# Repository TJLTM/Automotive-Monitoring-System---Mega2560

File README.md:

# Automotive-Monitoring-System---Mega2560
OpenSource monitoring system for older vehicles without OBDII. History for this project to give some insight in why i have it designed it as i have. My dad has a 1972 ford bronco that is used to go 4x4ing and it has since the day he bought it new over heated on trails while his friends 1970 stock bronco would be idling behind his vapor locked car on the trail. Mostly this is to solve that problem by providing data. Given data systems can be fixed. I based this on a MEGA2560 because of the number of I/O pins and real time nature of this. I may in the future switch this to SBC based but so far other than a few limitations has worked. 

What is logged: 
1. Fuel Pressure x 2
2. Tempetatures x 6
3. Manifold Vacuum x 2
4. AFR x 2
5. Battery Voltage
6. Current drawn from Alternator 
7. RPM 
8. Oil Pressure
9. GPS Data

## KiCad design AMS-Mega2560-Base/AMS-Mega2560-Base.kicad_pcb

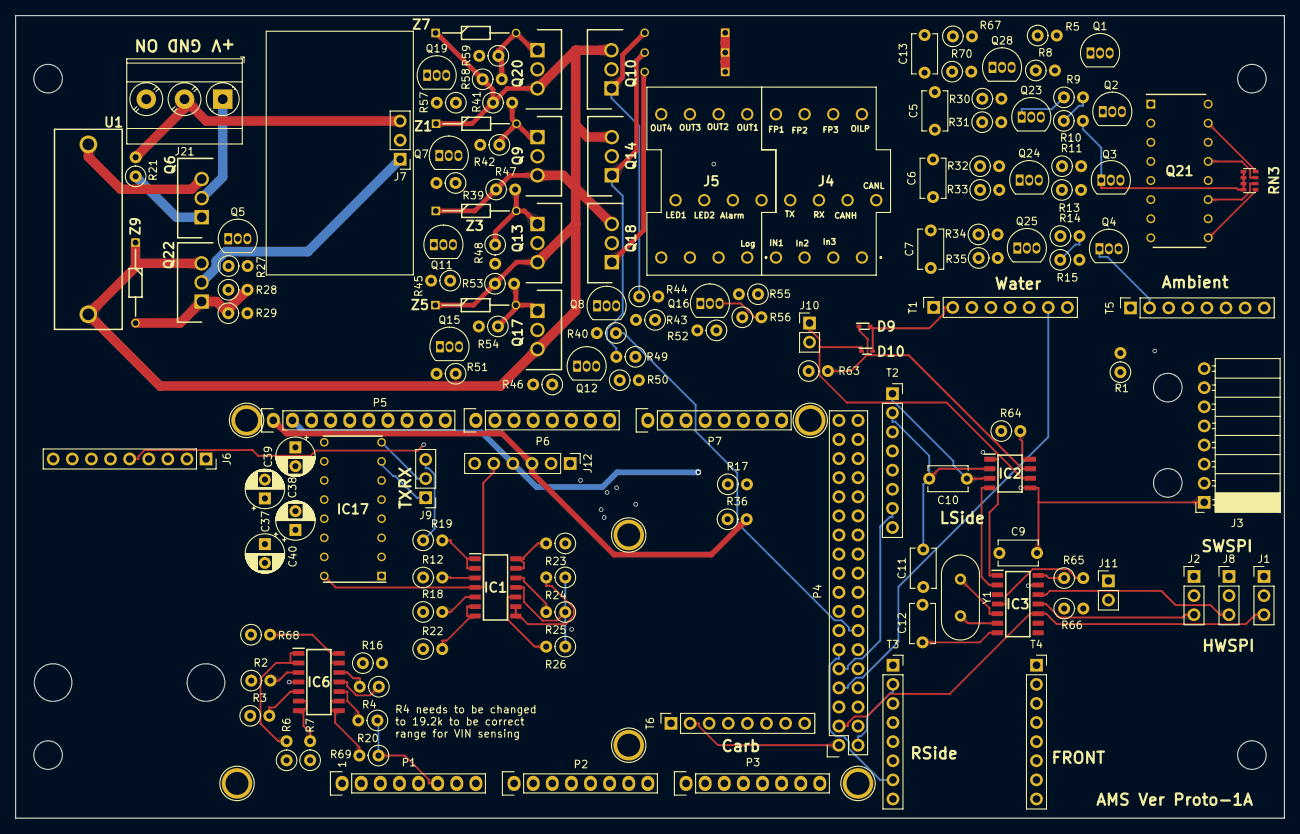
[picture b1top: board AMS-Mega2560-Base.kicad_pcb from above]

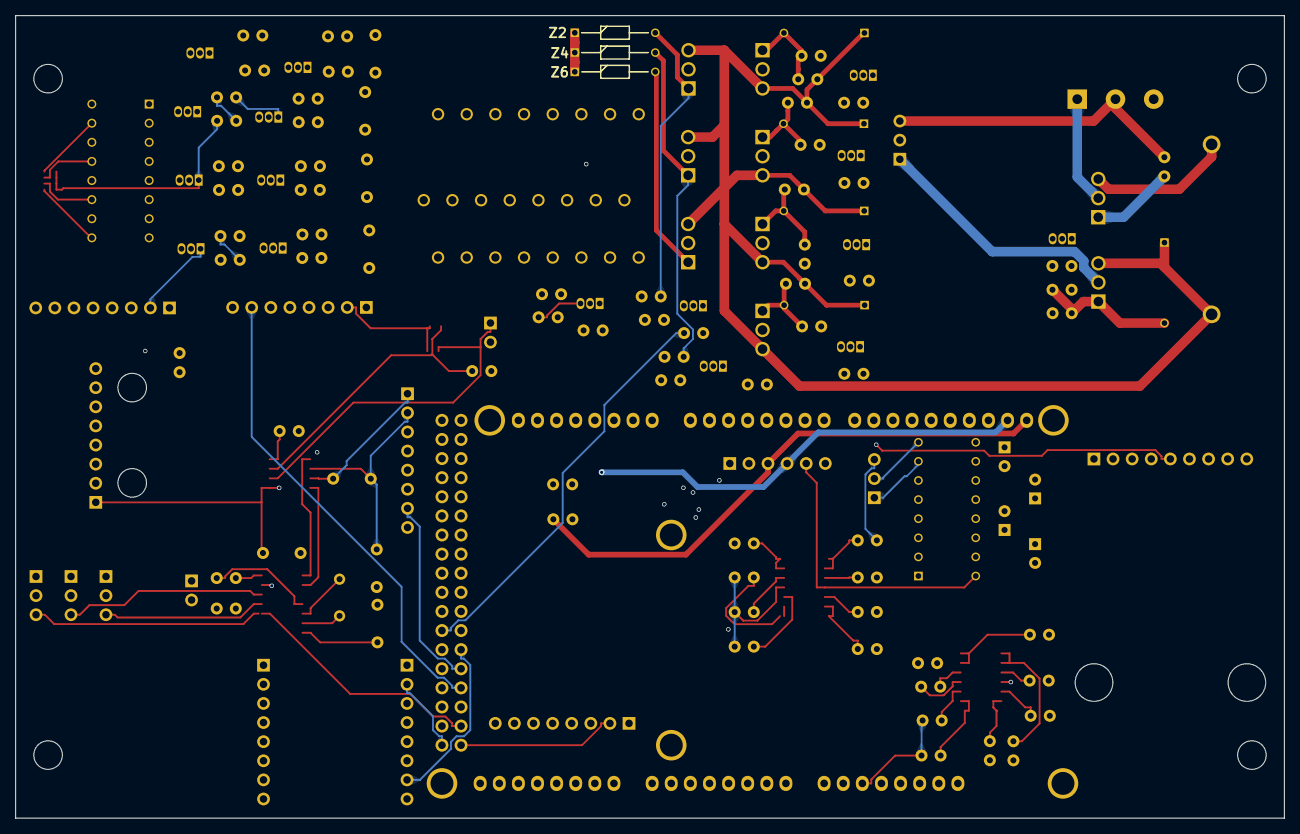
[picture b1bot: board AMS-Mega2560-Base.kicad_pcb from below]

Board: 4 copper layers, 168.7 x 106.7 mm, 153 parts (3 on the bottom side), 130 nets.

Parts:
C5, C6, C7, C13: 220nF; C_Disc_D5.1mm_W3.2mm_P5.00mm
C9: 0.1uF; C_Disc_D5.1mm_W3.2mm_P5.00mm
C10: 100nF; C_Disc_D5.1mm_W3.2mm_P5.00mm
C11, C12: 22pF; C_Disc_D5.1mm_W3.2mm_P5.00mm
C37, C38, C39, C40: 1uF; CP_Radial_D5.0mm_P2.50mm
D9, D10: ESD5Z5.0T1G; SODFL1608X70N
IC1, IC6: OPA4340UA; SOIC127P600X175-14N
IC2: MCP2542FD-H_SN; SOIC127P600X175-8N
IC3: MCP2518FDT-E_SL; SOIC127P600X175-14N
IC17: MAX232CPE+; DIP762W56P254L1918H457Q16N
J1, J2, J7, J8, J9: Conn_01x03; PinHeader_1x03_P2.54mm_Vertical
J3: Conn_01x08; PinSocket_1x08_P2.54mm_Horizontal
J4: Sense1; 1727751
J5: Sense2; 1727751
J6: AdafruitUltimateGPS; PinSocket_1x09_P2.54mm_Vertical
J10, J11: Conn_01x02; PinHeader_1x02_P2.54mm_Vertical
J12: Conn_01x06; PinHeader_1x06_P2.54mm_Vertical
J21: Screw_Terminal_01x03; TerminalBlock_Phoenix_MKDS-3-3-5.08_1x03_P5.08mm_Horizontal
P1: Power; Socket_Strip_Arduino_1x08
P2, P3: Analog; Socket_Strip_Arduino_1x08
P4: Digital; Socket_Strip_Arduino_2x18
P5: PWM; Socket_Strip_Arduino_1x10
P6: PWM; Socket_Strip_Arduino_1x08
P7: Communication; Socket_Strip_Arduino_1x08
P8, P9, P10, P11, P12, P13: CONN_01X01; Arduino_1pin
Q1, Q2, Q3, Q4, Q5, Q7, Q8, Q11, Q12, Q15, Q16, Q19: 2N7000; TO-92_Inline
Q6, Q9, Q10, Q13, Q14, Q17, Q18, Q20, Q22: IRF9Z34NPBF; TO254P469X1042X1967-3P
Q21: LTV-847; DIP762W60P254L1984H450Q16N
Q23, Q24, Q25, Q28: BS250; TO-92_Inline
R1, R6, R7, R19, R22, R23, R24, R68, R69: 47K; R_Axial_DIN0207_L6.3mm_D2.5mm_P2.54mm_Vertical
R2, R3, R4, R12, R18, R20, R25, R26: 100K; R_Axial_DIN0207_L6.3mm_D2.5mm_P2.54mm_Vertical
R5, R9, R11, R14: 470; R_Axial_DIN0207_L6.3mm_D2.5mm_P2.54mm_Vertical
R8, R10, R13, R15: 5k; R_Axial_DIN0207_L6.3mm_D2.5mm_P2.54mm_Vertical
R16, R65, R66: 47k; R_Axial_DIN0207_L6.3mm_D2.5mm_P2.54mm_Vertical
R17, R36: 2.2k; R_Axial_DIN0207_L6.3mm_D2.5mm_P2.54mm_Vertical
R21: 4.7K; R_Axial_DIN0207_L6.3mm_D2.5mm_P2.54mm_Vertical
R27, R28, R41, R43, R47, R49, R53, R55, R58: 100k; R_Axial_DIN0207_L6.3mm_D2.5mm_P2.54mm_Vertical
R29, R42, R44, R48, R50, R54, R56, R59, R64: 10k; R_Axial_DIN0207_L6.3mm_D2.5mm_P2.54mm_Vertical
R30, R32, R34, R67: 330; R_Axial_DIN0207_L6.3mm_D2.5mm_P2.54mm_Vertical
R31, R33, R35, R70: 1K; R_Axial_DIN0207_L6.3mm_D2.5mm_P2.54mm_Vertical
R39, R40, R45, R46, R51, R52, R57: 1M; R_Axial_DIN0207_L6.3mm_D2.5mm_P2.54mm_Vertical
R63: 120; R_Axial_DIN0207_L6.3mm_D2.5mm_P2.54mm_Vertical
RN3: EXB-38V223JV; EXB38V472JV
T1, T2, T3, T4, T5, T6: Conn_01x08; PinSocket_1x08_P2.54mm_Vertical
U1: BK_HTC-15M
Y1: Crystal; Crystal_HC49-U_Vertical
Z1, Z2, Z3, Z4, Z5, Z6, Z7, Z9: BZX79C10; DIOAD1068W53L380D172

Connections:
+5V: C9.2, C10.1, C40.2, IC1.4 (V+), IC2.3 (VDD), IC2.5 (VIO), IC3.14 (VDD), IC6.4 (V+), IC17.16 (VCC), J3.1, J6.8, J7.2, J12.5, P1.5, Q21.1 (ANODE_1), Q21.3 (ANODE_2), Q21.5 (ANODE_3), Q21.7 (ANODE_4), Q21.10 (COLLECTOR_1), Q21.12 (COLLECTOR_2), Q21.14 (COLLECTOR_3), Q21.16 (COLLECTOR_4), R1.1, R17.1, R36.1, R65.1, T1.1, T2.1, T3.1, T4.1, T5.1, T6.1
+VDC: Q9.3, Q10.3, Q13.3, Q14.3, Q17.3, Q18.3, Q20.3, Q22.3, R28.1, R41.1, R43.1, R47.1, R49.1, R53.1, R55.1, R58.1, U1.2, Z1.1, Z2.1, Z3.1, Z4.1, Z5.1, Z6.1, Z7.1, Z9.1
/BufferedADC1/ADCIN4: IC6.12 (+IN_D), R4.2, R16.2
/CAN Bus/CAN_INT: IC3.4 (~INT), J11.1, R65.2, R66.1
/Sheet6152913C/RSCOM2RX: IC17.8 (R2IN), J9.2
/Sheet6152913C/RSCOM2TX: IC17.7 (T2OUT), J9.1
AmbientCS: P4.15, T5.7
CANCS: IC3.13 (NCS), P4.23
CAN_INT: J11.2, P4.27
CAN_TX_STBY: IC2.8 (STBY), P4.25, R64.2
CarbCS: P4.17, T6.7
Com1RX: IC17.12 (R1OUT), P7.4
Com1TX: IC17.11 (T1IN), P7.3
Com2RX: IC17.9 (R2OUT), P7.6
Com2TX: IC17.10 (T2IN), P7.5
FrontCS: P4.13, T4.7
FuelPressure1: IC6.1 (OUT_A), IC6.2 (-IN_A), P2.3, R6.2
FuelPressure2: IC6.6 (-IN_B), IC6.7 (OUT_B), P2.4, R7.2
FuelPressure3: IC6.8 (OUT_C), IC6.9 (-IN_C), P2.5, R69.2
GND: C5.2, C6.2, C7.2, C9.1, C10.2, C11.2, C12.2, C13.2, C39.1, D9.2, D10.2, IC1.11 (V-), IC2.2 (VSS), IC3.7 (VSS), IC6.11 (V-), IC17.15 (GND), J3.3, J6.7, J7.3, J9.3, J12.6, J21.2, P1.6, P1.7, P4.1, P4.2, P5.4, Q1.1 (S), Q2.1 (S), Q3.1 (S), Q4.1 (S), Q5.1 (S), Q7.1 (S), Q8.1 (S), Q11.1 (S), Q12.1 (S), Q15.1 (S), Q16.1 (S), Q19.1 (S), R2.1, R3.1, R4.1, R6.1, R7.1, R8.2, R10.2, R12.1, R13.2, R15.2, R18.1, R19.1, R20.1, R21.2, R22.1, R23.1, R24.1, R25.1, R26.1, R27.2, R30.2, R32.2, R34.2, R39.2, R40.2, R45.2, R46.2, R51.2, R52.2, R57.2, R64.1, R66.2, R67.2, R68.1, R69.1, RN3.1, RN3.2, RN3.3, RN3.4, T1.2, T2.2, T3.2, T4.2, T5.2, T6.2
GPSBat: J6.3, P2.2
GPSRX: J6.6, P7.1
GPSTX: J6.5, P7.2
IN1TTL: P6.6, Q21.15 (EMITTER_4), RN3.8
IN2TTL: P6.5, Q21.13 (EMITTER_3), RN3.7
IN3TTL: P4.10, Q21.11 (EMITTER_2), RN3.6
Logging: P4.8, Q21.9 (EMITTER_1), RN3.5
LsideCS: P4.9, T2.7
MISO: IC3.11 (SDI), J2.3, J3.5, P4.5
MOSI: IC3.12 (SDO), J3.6, J8.3, P4.6
unnamed: J21.1, Q6.2
unnamed: Q6.3, U1.1
unnamed: C39.2, IC17.6 (V-)
unnamed: C40.1, IC17.2 (V+)
unnamed: IC2.4 (RXD), IC3.2 (RXCAN)
unnamed: IC2.1 (TXD), IC3.1 (TXCAN)
unnamed: C12.1, IC3.6 (OSC1), Y1.2
unnamed: C11.1, IC3.5 (OSC2), Y1.1
unnamed: C37.1, IC17.1 (C1+)
unnamed: C37.2, IC17.3 (C1-)
unnamed: C38.1, IC17.4 (C2+)
unnamed: C38.2, IC17.5 (C2-)
unnamed: J10.2, R63.1
unnamed: Q1.3 (D), R70.1
unnamed: Q1.2 (G), R5.2, R8.1
unnamed: Q2.3 (D), R31.1
unnamed: Q2.2 (G), R9.2, R10.1
unnamed: Q3.3 (D), R33.1
unnamed: Q3.2 (G), R11.2, R13.1
unnamed: Q4.3 (D), R35.1
unnamed: Q4.2 (G), R14.2, R15.1
unnamed: Q5.3 (D), R29.2
unnamed: Q6.1, R21.1
unnamed: Q7.3 (D), R42.2
unnamed: Q8.3 (D), R44.2
unnamed: Q9.1, R41.2, R42.1, Z1.2
unnamed: Q10.1, R43.2, R44.1, Z2.2
unnamed: Q11.3 (D), R48.2
unnamed: Q12.3 (D), R50.2
unnamed: Q13.1, R47.2, R48.1, Z3.2
unnamed: Q14.1, R49.2, R50.1, Z4.2
unnamed: Q15.3 (D), R54.2
unnamed: Q16.3 (D), R56.2
unnamed: Q17.1, R53.2, R54.1, Z5.2
unnamed: Q18.1, R55.2, R56.1, Z6.2
unnamed: Q19.3 (D), R59.2
unnamed: Q20.1, R58.2, R59.1, Z7.2
unnamed: Q21.2 (CATHODE_1), R70.2
unnamed: Q21.4 (CATHODE_2), R31.2
unnamed: Q21.6 (CATHODE_3), R33.2
unnamed: Q21.8 (CATHODE_4), R35.2
unnamed: Q22.1, R28.2, R29.1, Z9.2
unnamed: Q23.1 (D), R9.1
unnamed: Q23.2 (G), R30.1
unnamed: Q24.1 (D), R11.1
unnamed: Q24.2 (G), R32.1
unnamed: Q25.1 (D), R14.1
unnamed: Q25.2 (G), R34.1
unnamed: Q28.1 (D), R5.1
unnamed: Q28.2 (G), R67.1
OUTPUT1: P6.4, Q19.2 (G), R57.1
OUTPUT2: P6.3, Q7.2 (G), R39.1
OUTPUT3: P6.2, Q11.2 (G), R45.1
OUTPUT4: P6.1, Q15.2 (G), R51.1
OUTPUTLED1: P4.14, Q8.2 (G), R40.1
OUTPUTLED2: P4.12, Q12.2 (G), R46.1
OUTPUTSiren: P5.10, Q16.2 (G), R52.1
OilPressure: IC1.1 (OUT_A), IC1.2 (-IN_A), P2.6, R19.2
PowerOn: J21.3, Q5.2 (G), R27.1
RTDMISO: J2.2, T1.5, T2.5, T3.5, T4.5, T5.5, T6.5
RTDMOSI: J8.2, T1.6, T2.6, T3.6, T4.6, T5.6, T6.6
RTDSCLK: J1.2, T1.4, T2.4, T3.4, T4.4, T5.4, T6.4
RsideCS: P4.11, T3.7
SCL: J12.3, P5.1, P7.8, R36.2
SCLK: IC3.10 (SCK), J1.3, J3.4, P4.3
SDA: J12.4, P5.2, P7.7, R17.2
SDCS: J3.7, P4.19
SDDetect: J3.8, P4.21, R1.2
SWMISO: J2.1, P4.32
SWMOSI: J8.1, P4.34
SWSCLK: J1.1, P4.30
Sense1-1: J4.1, P3.2
Sense1-2: D10.1, IC2.6 (CANL), J4.2, J10.1
Sense1-3: IC1.3 (+IN_A), J4.3, R12.2
Sense1-4: C6.1, J4.4, Q24.3 (S)
Sense1-5: D9.1, IC2.7 (CANH), J4.5, R63.2
Sense1-6: IC6.10 (+IN_C), J4.6, R20.2
Sense1-7: C5.1, J4.7, Q23.3 (S)
Sense1-8: IC17.13 (R1IN), J4.8
Sense1-9: IC6.5 (+IN_B), J4.9, R3.2
Sense1-10: C13.1, J4.10, Q28.3 (S)
Sense1-11: IC17.14 (T1OUT), J4.11
Sense1-12: IC6.3 (+IN_A), J4.12, R2.2
Sense2-1: C7.1, J5.1, Q25.3 (S)
Sense2-3: J5.3, Q20.2
Sense2-4: IC1.12 (+IN_D), J5.4, R25.2
Sense2-5: J5.5, Q18.2
Sense2-6: J5.6, Q9.2
Sense2-7: IC1.10 (+IN_C), J5.7, R26.2
Sense2-8: J5.8, Q14.2
Sense2-9: J5.9, Q13.2
Sense2-10: IC1.5 (+IN_B), J5.10, R18.2
Sense2-11: J5.11, Q10.2
Sense2-12: J5.12, Q17.2
SpareADC1: IC1.6 (-IN_B), IC1.7 (OUT_B), P2.7, R22.2
SpareADC2: IC1.8 (OUT_C), IC1.9 (-IN_C), P2.8, R24.2
SpareADC3: IC1.13 (-IN_D), IC1.14 (OUT_D), P3.1, R23.2
VPP: J7.1, Q22.2, R16.1
VoltageSensor: IC6.13 (-IN_D), IC6.14 (OUT_D), P2.1, R68.2
WaterCS: P4.7, T1.7

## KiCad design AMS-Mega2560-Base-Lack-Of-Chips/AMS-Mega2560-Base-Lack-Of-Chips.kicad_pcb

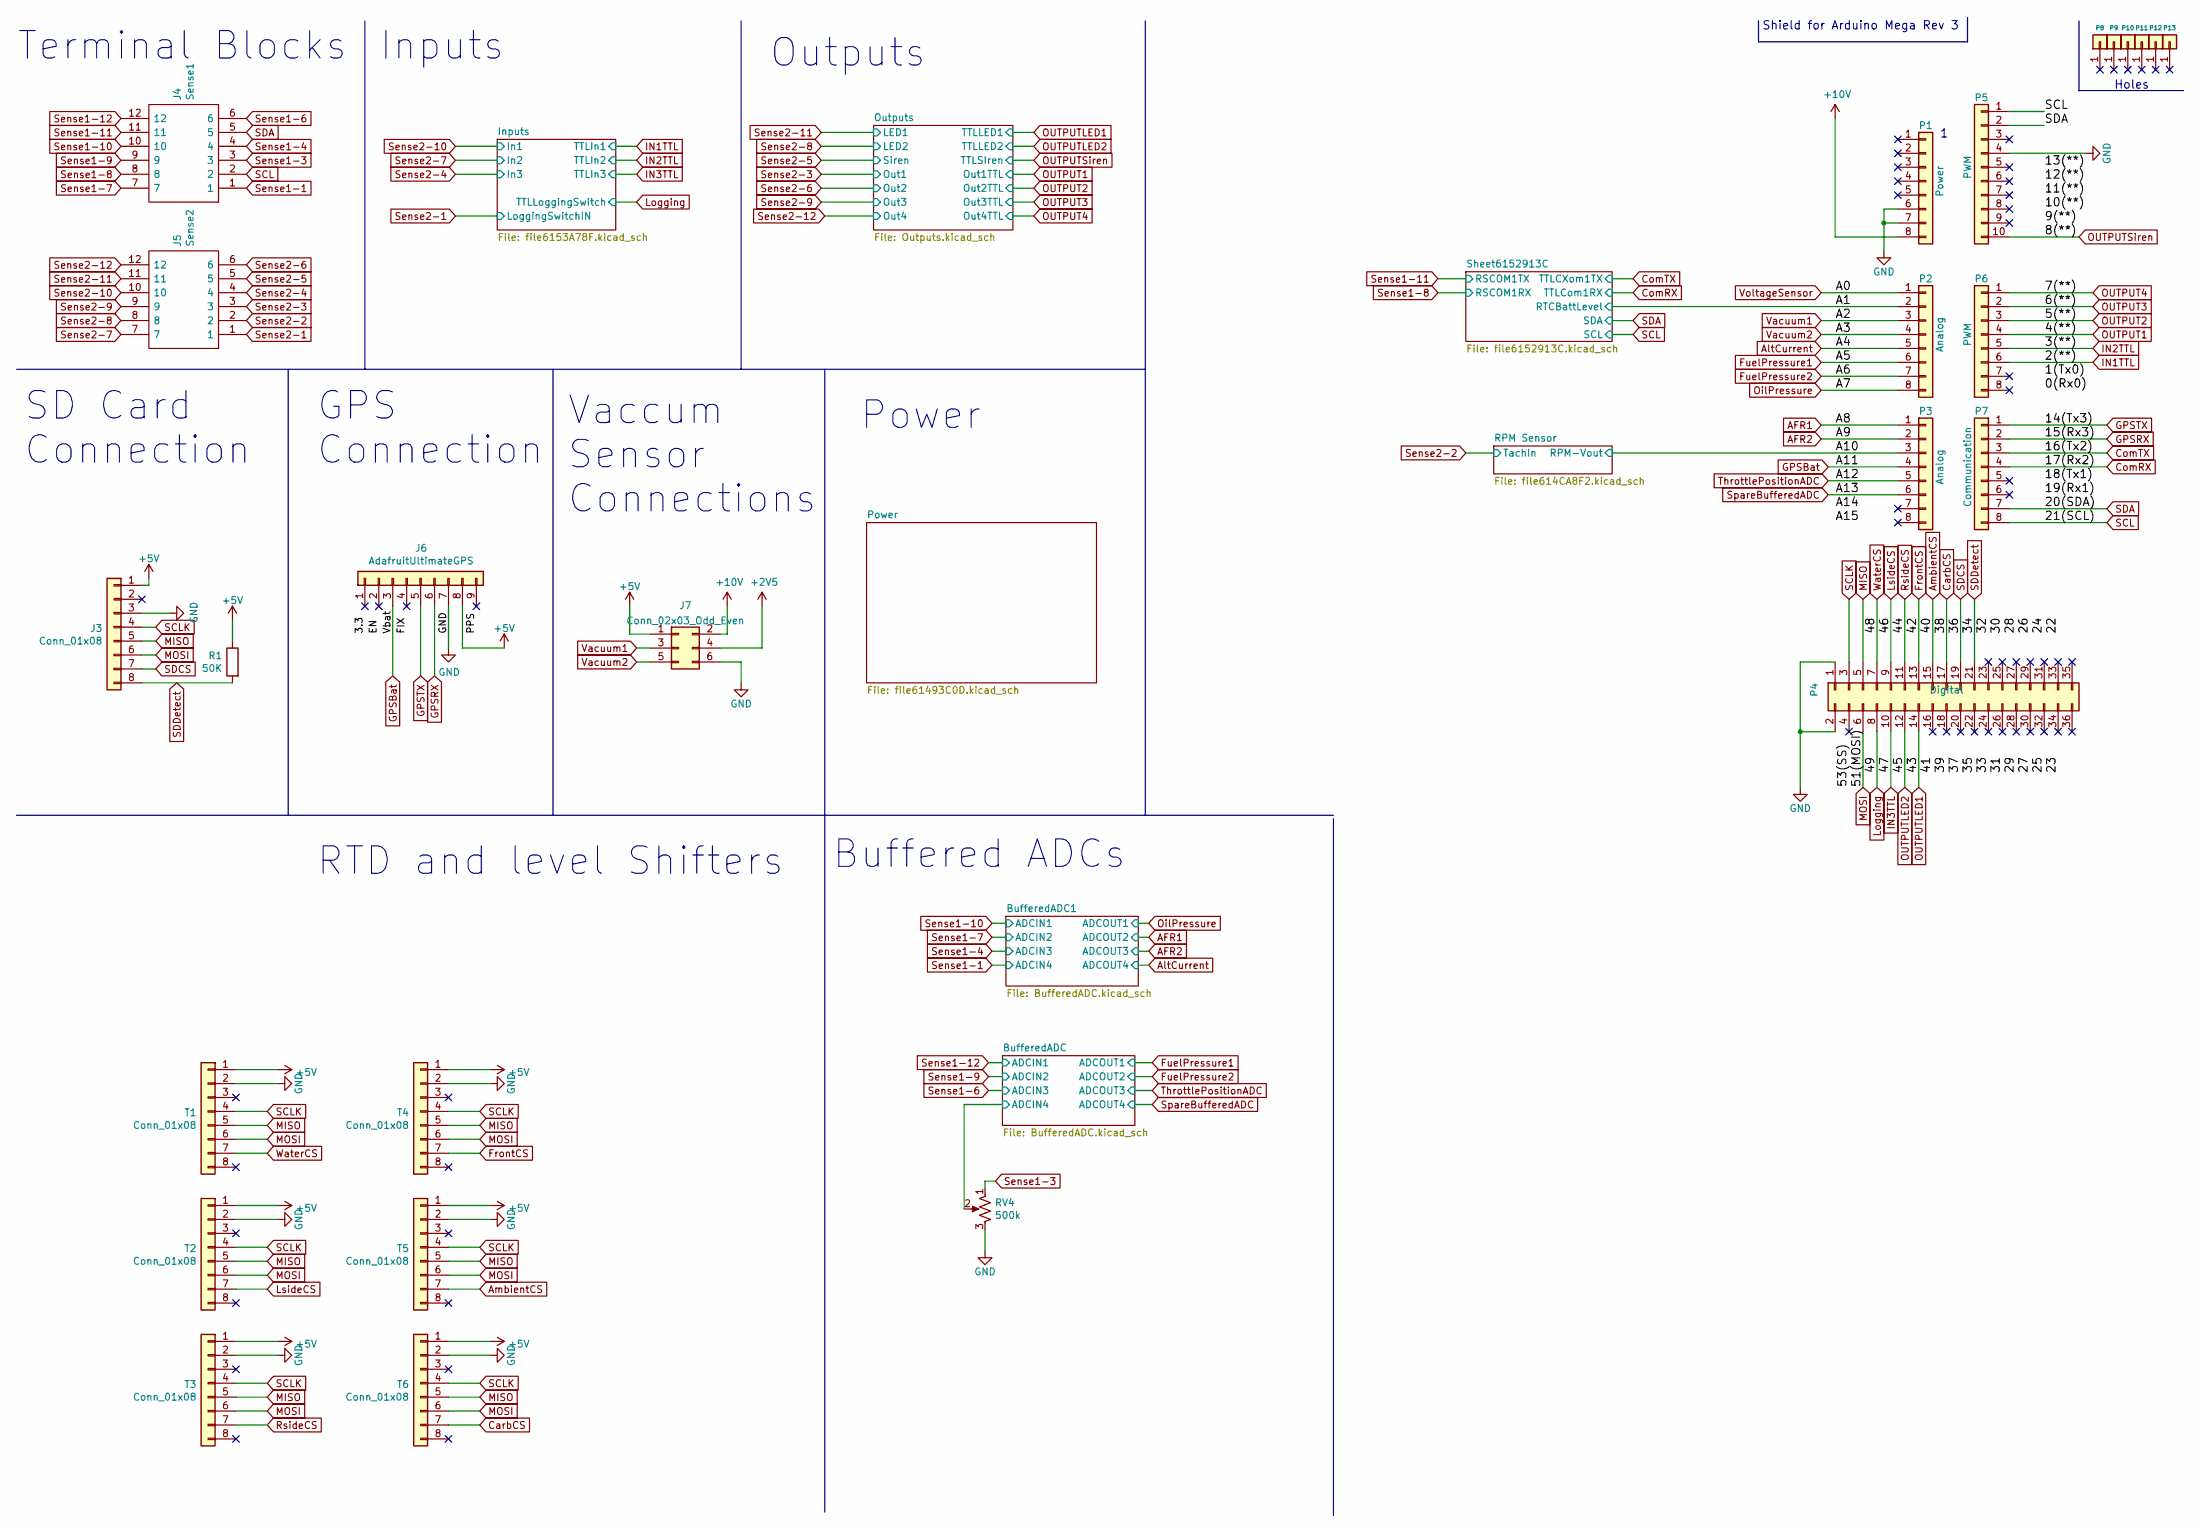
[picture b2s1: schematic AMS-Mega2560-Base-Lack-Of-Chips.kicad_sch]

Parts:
J3: Conn_01x08; PinSocket_1x08_P2.54mm_Horizontal
J4: Sense1; 1727751; Mouser Part Number 651-1727751
J5: Sense2; 1727751; Mouser Part Number 651-1727751
J6: AdafruitUltimateGPS; PinSocket_1x09_P2.54mm_Vertical
J7: Conn_02x03_Odd_Even; PinHeader_2x03_P2.54mm_Vertical
P1: Power; Socket_Strip_Arduino_1x08
P2, P3: Analog; Socket_Strip_Arduino_1x08
P4: Digital; Socket_Strip_Arduino_2x18
P5: PWM; Socket_Strip_Arduino_1x10
P6: PWM; Socket_Strip_Arduino_1x08
P7: Communication; Socket_Strip_Arduino_1x08
P8, P9, P10, P11, P12, P13: CONN_01X01; Arduino_1pin
R1: 50K; R_Axial_DIN0207_L6.3mm_D2.5mm_P2.54mm_Vertical
RV4: 500k; Potentiometer_Bourns_3296W_Vertical
T1, T2, T3, T4, T5, T6: Conn_01x08; PinSocket_1x08_P2.54mm_Vertical

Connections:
+2V5: J7.4; also elsewhere on the board
/A1: P2.2; also elsewhere on the board
/A10: P3.3; also elsewhere on the board
/BufferedADC/ADCIN4: RV4.2; also elsewhere on the board
AFR1: P3.1; also elsewhere on the board
AFR2: P3.2; also elsewhere on the board
AltCurrent: P2.5; also elsewhere on the board
AmbientCS: P4.15, T5.7
CarbCS: P4.17, T6.7
ComRX: P7.4; also elsewhere on the board
ComTX: P7.3; also elsewhere on the board
FrontCS: P4.13, T4.7
FuelPressure1: P2.6; also elsewhere on the board
FuelPressure2: P2.7; also elsewhere on the board
GPSBat: J6.3, P3.4
GPSRX: J6.6, P7.2
GPSTX: J6.5, P7.1
IN1TTL: P6.6; also elsewhere on the board
IN2TTL: P6.5; also elsewhere on the board
Logging: P4.8; also elsewhere on the board
LsideCS: P4.9, T2.7
MISO: J3.5, P4.5, T1.5, T2.5, T3.5, T4.5, T5.5, T6.5
MOSI: J3.6, P4.6, T1.6, T2.6, T3.6, T4.6, T5.6, T6.6
OUTPUT1: P6.4; also elsewhere on the board
OUTPUT2: P6.3; also elsewhere on the board
OUTPUT3: P6.2; also elsewhere on the board
OUTPUT4: P6.1; also elsewhere on the board
OUTPUTLED1: P4.14; also elsewhere on the board
OUTPUTLED2: P4.12; also elsewhere on the board
OUTPUTSiren: P5.10; also elsewhere on the board
OilPressure: P2.8; also elsewhere on the board
RsideCS: P4.11, T3.7
SCL: J4.2, P5.1, P7.8; also elsewhere on the board
SCLK: J3.4, P4.3, T1.4, T2.4, T3.4, T4.4, T5.4, T6.4
SDA: J4.5, P5.2, P7.7; also elsewhere on the board
SDCS: J3.7, P4.19
SDDetect: J3.8, P4.21, R1.2
Sense1-3: J4.3, RV4.1
Sense1-6: J4.6; also elsewhere on the board
Sense1-8: J4.8; also elsewhere on the board
Sense1-9: J4.9; also elsewhere on the board
Sense1-11: J4.11; also elsewhere on the board
Sense1-12: J4.12; also elsewhere on the board
Sense2-1: J5.1; also elsewhere on the board
Sense2-2: J5.2; also elsewhere on the board
Sense2-3: J5.3; also elsewhere on the board
Sense2-4: J5.4; also elsewhere on the board
Sense2-5: J5.5; also elsewhere on the board
Sense2-6: J5.6; also elsewhere on the board
Sense2-7: J5.7; also elsewhere on the board
Sense2-8: J5.8; also elsewhere on the board
Sense2-9: J5.9; also elsewhere on the board
Sense2-10: J5.10; also elsewhere on the board
Sense2-11: J5.11; also elsewhere on the board
Sense2-12: J5.12; also elsewhere on the board
SpareBufferedADC: P3.6; also elsewhere on the board
ThrottlePositionADC: P3.5; also elsewhere on the board
Vacuum1: J7.3, P2.3
Vacuum2: J7.5, P2.4
VoltageSensor: P2.1; also elsewhere on the board
WaterCS: P4.7, T1.7

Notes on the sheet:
Holes
Shield for Arduino Mega Rev 3
Outputs
Vaccum Sensor Connections
SD Card Connection
Inputs
Buffered ADCs
GPS Connection
Terminal Blocks
RTD and level Shifters
Power

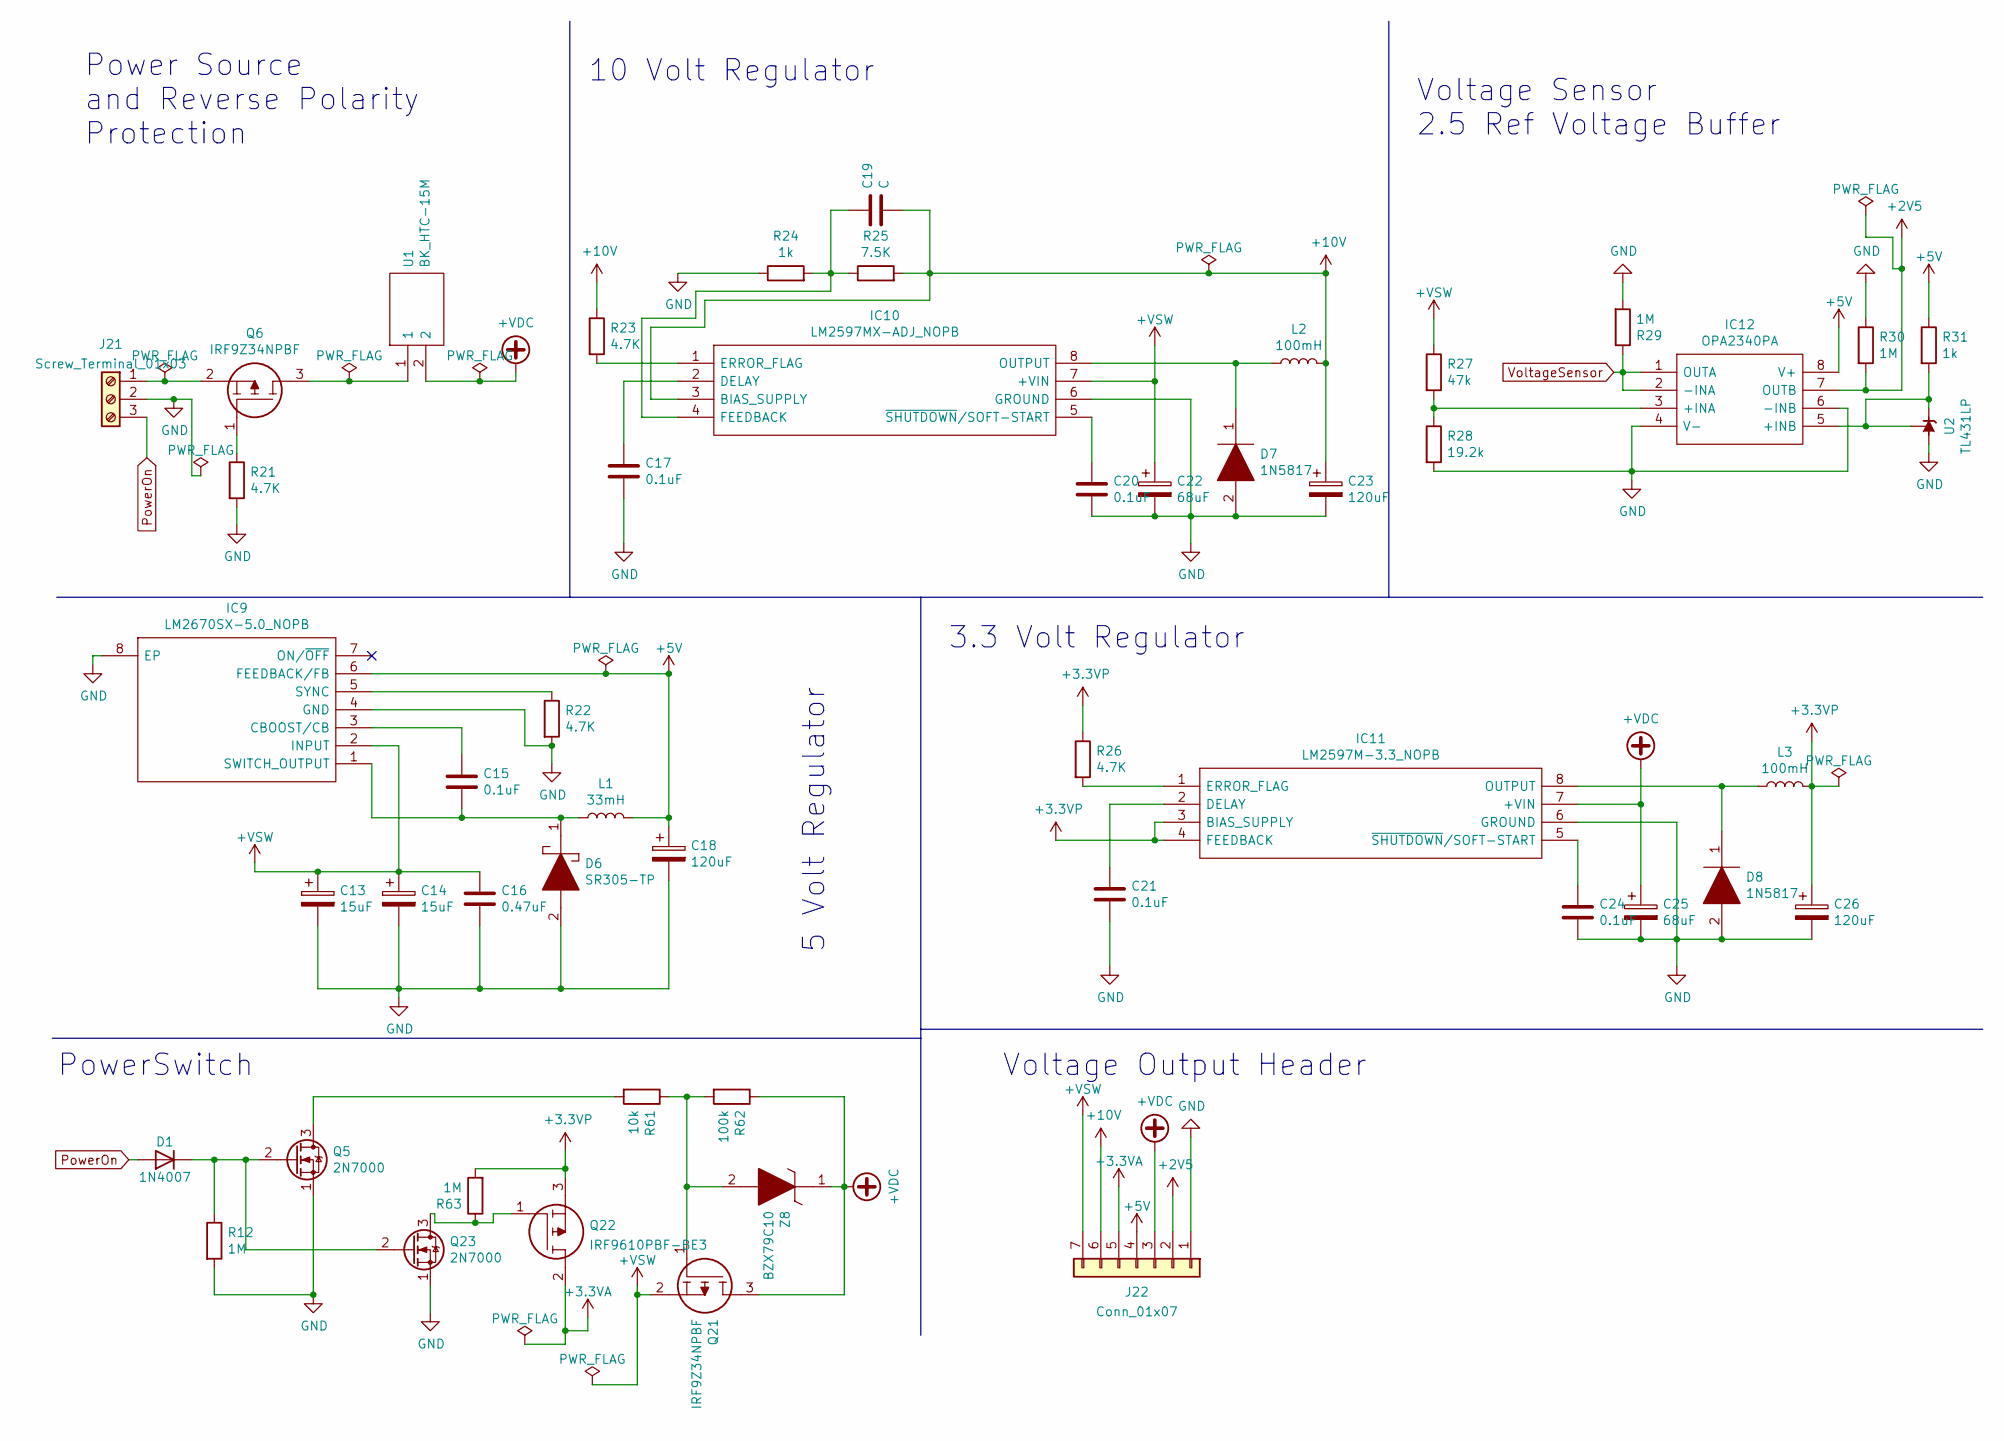
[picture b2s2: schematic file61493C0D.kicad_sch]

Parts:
C13, C14: 15uF; CP_Radial_D5.0mm_P2.50mm
C15, C17, C20, C21, C24: 0.1uF; C_Rect_L9.0mm_W3.6mm_P7.50mm_MKT
C16: 0.47uF; C_Rect_L9.0mm_W3.6mm_P7.50mm_MKT
C18, C23, C26: 120uF; CP_Radial_D8.0mm_P5.00mm
C19: C; C_Rect_L9.0mm_W3.6mm_P7.50mm_MKT
C22, C25: 68uF; CP_Radial_D5.0mm_P2.50mm
D1: 1N4007; D_DO-41_SOD81_P10.16mm_Horizontal
D6: SR305-TP; DIOAD2860W130L840D505; Mouser Part Number 833-SR305-TP
D7, D8: 1N5817; DIOAD1414W86L464D238; Mouser Part Number 511-1N5817
IC9: LM2670SX-5.0_NOPB; LM2670SX50NOPB; Mouser Part Number 926-LM2670SX50NOPB
IC10: LM2597MX-ADJ_NOPB; SOIC127P600X175-8N; Mouser Part Number 926-LM2597MXADJNOPB
IC11: LM2597M-3.3_NOPB; SOIC127P600X175-8N; Mouser Part Number 926-LM2597M-33/NOPB
IC12: OPA2340PA; DIP794W53P254L959H508Q8N; Mouser Part Number 595-OPA2340PA
J21: Screw_Terminal_01x03; TerminalBlock_Phoenix_MKDS-3-3-5.08_1x03_P5.08mm_Horizontal
J22: Conn_01x07; PinHeader_1x07_P2.54mm_Vertical
L1: 33mH; L_Axial_L9.5mm_D4.0mm_P15.24mm_Horizontal_Fastron_SMCC
L2, L3: 100mH; L_Axial_L9.5mm_D4.0mm_P15.24mm_Horizontal_Fastron_SMCC
Q5, Q23: 2N7000; TO-92_Inline
Q6, Q21: IRF9Z34NPBF; TO254P469X1042X1967-3P; Mouser Part Number 942-IRF9Z34NPBF
Q22: IRF9610PBF-BE3; TO254P465X1024X2050-3P; Mouser Part Number 78-IRF9610PBF-BE3
R12, R29, R30, R63: 1M; R_Axial_DIN0207_L6.3mm_D2.5mm_P2.54mm_Vertical
R21, R22, R23, R26: 4.7K; R_Axial_DIN0207_L6.3mm_D2.5mm_P2.54mm_Vertical
R24, R31: 1k; R_Axial_DIN0207_L6.3mm_D2.5mm_P2.54mm_Vertical
R25: 7.5K; R_Axial_DIN0207_L6.3mm_D2.5mm_P2.54mm_Vertical
R27: 47k; R_Axial_DIN0207_L6.3mm_D2.5mm_P2.54mm_Vertical
R28: 19.2k; R_Axial_DIN0207_L6.3mm_D2.5mm_P2.54mm_Vertical
R61: 10k; R_Axial_DIN0207_L6.3mm_D2.5mm_P2.54mm_Vertical
R62: 100k; R_Axial_DIN0207_L6.3mm_D2.5mm_P2.54mm_Vertical
U1: BK_HTC-15M; Mouser Part Number 504-HTC-15M
U2: TL431LP; TO-92_Inline
Z8: BZX79C10; DIOAD1068W53L380D172; Mouser Part Number 512-BZX79C10

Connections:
+2V5: IC12.7 (OUTB), J22.2, R30.2; also elsewhere on the board
+3.3VA: J22.5, Q22.2
+VDC: C25.1, IC11.7 (+VIN), J22.3, Q21.3, R62.1, U1.2, Z8.1; also elsewhere on the board
+VSW: C13.1, C14.1, C16.1, C22.1, IC9.2 (INPUT), IC10.7 (+VIN), J22.7, Q21.2, R27.1; also elsewhere on the board
unnamed: C15.1, IC9.3 (CBOOST/CB)
unnamed: C15.2, D6.1, IC9.1 (SWITCH_OUTPUT), L1.1
unnamed: C17.1, IC10.2 (DELAY)
unnamed: C20.1, IC10.5 (~SHUTDOWN/SOFT-START)
unnamed: C21.1, IC11.2 (DELAY)
unnamed: C24.1, IC11.5 (~SHUTDOWN/SOFT-START)
unnamed: D7.1, IC10.8 (OUTPUT), L2.1
unnamed: D8.1, IC11.8 (OUTPUT), L3.1
unnamed: IC9.5 (SYNC), R22.1
unnamed: IC10.1 (ERROR_FLAG), R23.2
unnamed: IC12.3 (+INA), R27.2, R28.1
unnamed: IC12.5 (+INB), R31.2, U2.1 (REF), U2.3 (K)
unnamed: J21.1, Q6.2
unnamed: Q5.3 (D), R61.2
unnamed: Q6.1, R21.1
unnamed: Q6.3, U1.1
unnamed: Q21.1, R61.1, R62.2, Z8.2
PowerOn: D1.2 (A), J21.3
VoltageSensor: IC12.1 (OUTA), IC12.2 (-INA), R29.1; also elsewhere on the board

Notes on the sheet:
Voltage Output Header
Voltage Sensor 2.5 Ref Voltage Buffer
5 Volt Regulator
PowerSwitch
10 Volt Regulator
3.3 Volt Regulator
Power Source and Reverse Polarity Protection

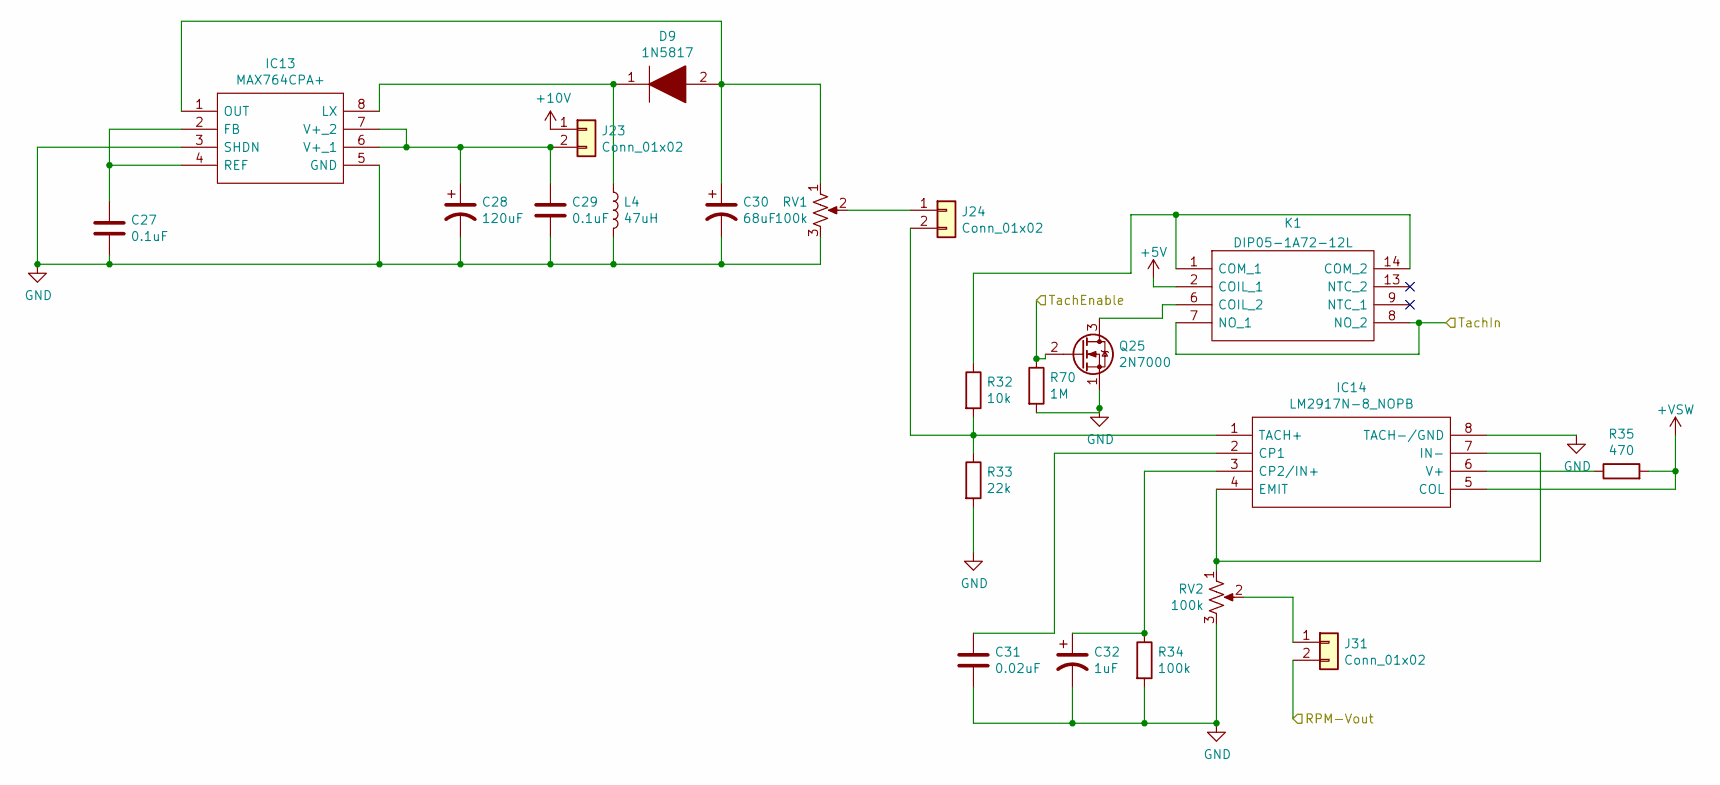
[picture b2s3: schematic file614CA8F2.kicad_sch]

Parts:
C27, C29: 0.1uF; C_Disc_D7.5mm_W5.0mm_P10.00mm
C28: 120uF; CP_Radial_D8.0mm_P5.00mm
C30: 68uF; CP_Radial_D8.0mm_P5.00mm
C31: 0.02uF; C_0805_2012Metric_Pad1.18x1.45mm_HandSolder
C32: 1uF; CP_Radial_D4.0mm_P1.50mm
D9: 1N5817; DIOAD1414W86L464D238; Mouser Part Number 511-1N5817
IC13: MAX764CPA+; DIP762W56P254L938H457Q8N; Mouser Part Number 700-MAX764CPA
IC14: LM2917N-8_NOPB; DIP794W53P254L959H508Q8N; Mouser Part Number 926-LM2917N-8/NOPB
J23, J24, J31: Conn_01x02; PinHeader_1x02_P2.54mm_Vertical
K1: DIP05-1A72-12L; DIP051A7212L; Mouser Part Number 876-DIP05-1A72-12L
L4: 47uH; L_Axial_L7.0mm_D3.3mm_P10.16mm_Horizontal_Fastron_MICC
Q25: 2N7000; TO-92_Inline
R32: 10k; R_Axial_DIN0207_L6.3mm_D2.5mm_P2.54mm_Vertical
R33: 22k; R_Axial_DIN0207_L6.3mm_D2.5mm_P2.54mm_Vertical
R34: 100k; R_Axial_DIN0207_L6.3mm_D2.5mm_P2.54mm_Vertical
R35: 470; R_Axial_DIN0207_L6.3mm_D2.5mm_P2.54mm_Vertical
R70: 1M; R_Axial_DIN0207_L6.3mm_D2.5mm_P2.54mm_Vertical
RV1, RV2: 100k; Potentiometer_Bourns_3296W_Vertical

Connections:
+VSW: IC14.5 (COL), R35.2; also elsewhere on the board
/A10: J31.2; also elsewhere on the board
unnamed: C27.1, IC13.2 (FB), IC13.4 (REF)
unnamed: C28.1, C29.1, IC13.6 (V+_1), IC13.7 (V+_2), J23.2
unnamed: C30.1, D9.2, IC13.1 (OUT), RV1.1
unnamed: C31.1, IC14.2 (CP1)
unnamed: C32.1, IC14.3 (CP2/IN+), R34.1
unnamed: D9.1, IC13.8 (LX), L4.1
unnamed: IC14.1 (TACH+), J24.2, R32.2, R33.1
unnamed: IC14.4 (EMIT), IC14.7 (IN-), RV2.1
unnamed: IC14.6 (V+), R35.1
unnamed: J24.1, RV1.2
unnamed: J31.1, RV2.2
unnamed: K1.1 (COM_1), K1.14 (COM_2), R32.1
unnamed: K1.6 (COIL_2), Q25.3 (D)
Sense2-2: K1.7 (NO_1), K1.8 (NO_2); also elsewhere on the board

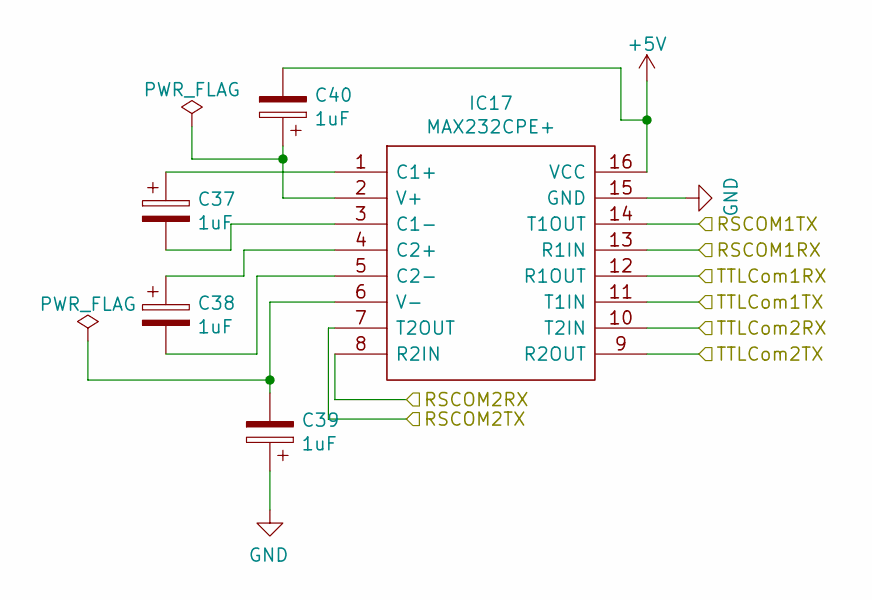
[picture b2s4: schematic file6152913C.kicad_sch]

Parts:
C37, C38, C39, C40: 1uF; CP_Radial_D5.0mm_P2.50mm
IC17: MAX232CPE+; DIP762W56P254L1918H457Q16N; Mouser Part Number 700-MAX232CPE

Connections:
ComRX: IC17.12 (R1OUT); also elsewhere on the board
ComTX: IC17.11 (T1IN); also elsewhere on the board
unnamed: C37.1, IC17.1 (C1+)
unnamed: C37.2, IC17.3 (C1-)
unnamed: C38.1, IC17.4 (C2+)
unnamed: C38.2, IC17.5 (C2-)
unnamed: C39.2, IC17.6 (V-)
unnamed: C40.1, IC17.2 (V+)
Sense1-8: IC17.13 (R1IN); also elsewhere on the board
Sense1-11: IC17.14 (T1OUT); also elsewhere on the board

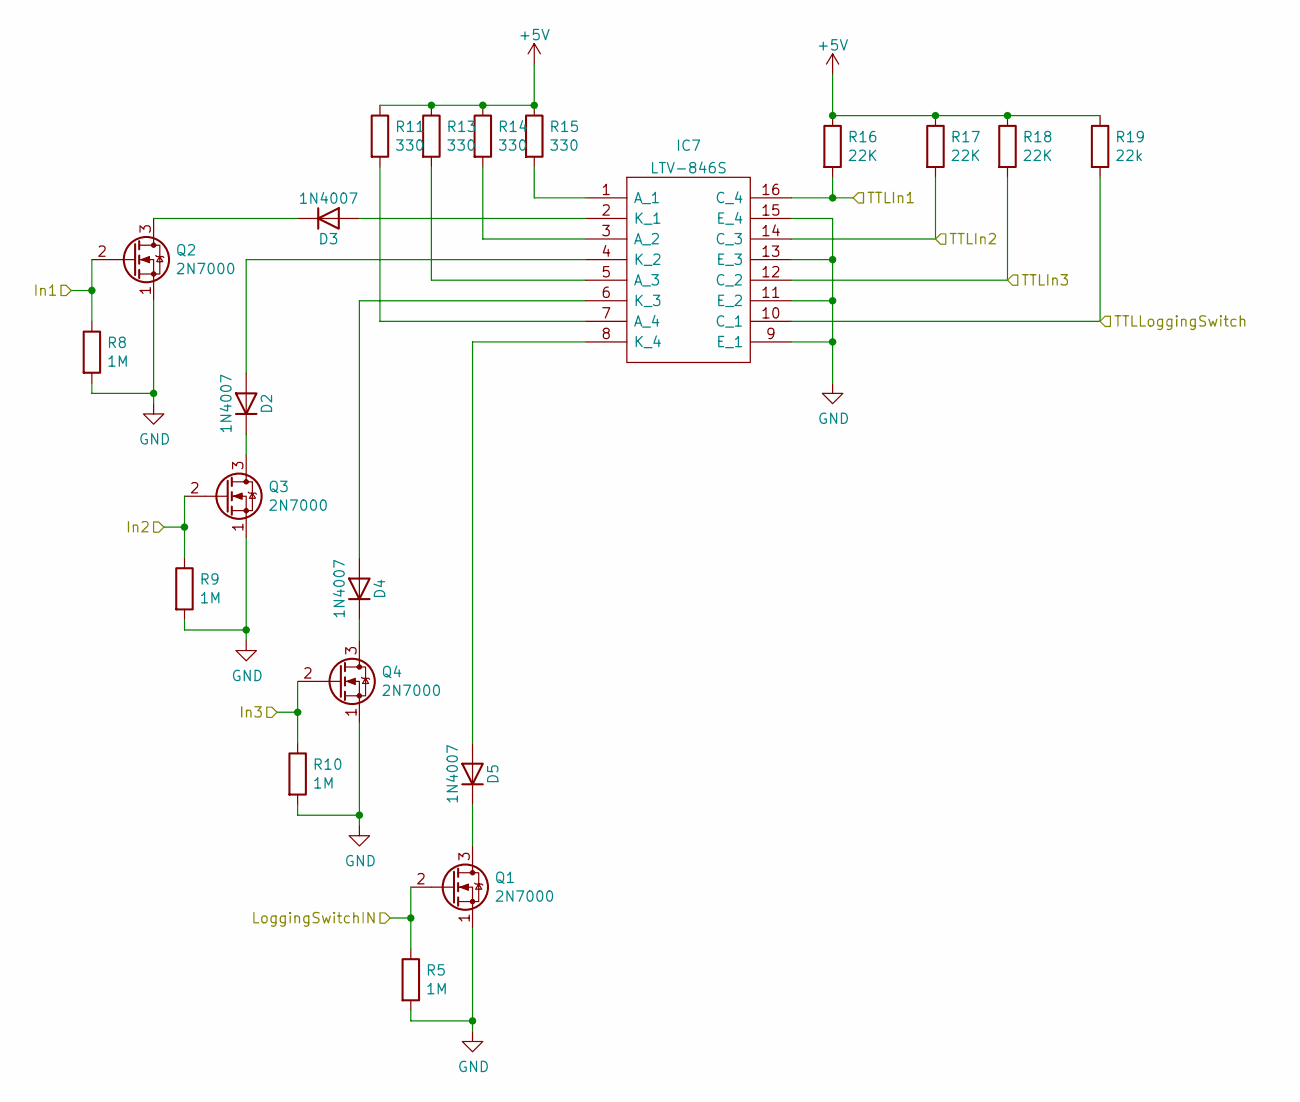
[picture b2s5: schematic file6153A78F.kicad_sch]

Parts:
D2, D3, D4, D5: 1N4007; D_DO-41_SOD81_P10.16mm_Horizontal
IC7: LTV-846S; SOP254P1016X460-16N; Mouser Part Number 859-LTV-846S
Q1, Q2, Q3, Q4: 2N7000; TO-92_Inline
R5, R8, R9, R10: 1M; R_Axial_DIN0207_L6.3mm_D2.5mm_P2.54mm_Vertical
R11, R13, R14, R15: 330; R_Axial_DIN0207_L6.3mm_D2.5mm_P2.54mm_Vertical
R16, R17, R18: 22K; R_Axial_DIN0207_L6.3mm_D2.5mm_P2.54mm_Vertical
R19: 22k; R_Axial_DIN0207_L6.3mm_D2.5mm_P2.54mm_Vertical

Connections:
IN1TTL: IC7.16 (C_4), R16.2; also elsewhere on the board
IN2TTL: IC7.14 (C_3), R17.2; also elsewhere on the board
Logging: IC7.10 (C_1), R19.2; also elsewhere on the board
unnamed: D2.1 (K), Q3.3 (D)
unnamed: D2.2 (A), IC7.4 (K_2)
unnamed: D3.1 (K), Q2.3 (D)
unnamed: D3.2 (A), IC7.2 (K_1)
unnamed: D4.1 (K), Q4.3 (D)
unnamed: D4.2 (A), IC7.6 (K_3)
unnamed: D5.1 (K), Q1.3 (D)
unnamed: D5.2 (A), IC7.8 (K_4)
unnamed: IC7.1 (A_1), R15.2
unnamed: IC7.3 (A_2), R14.2
unnamed: IC7.5 (A_3), R13.2
unnamed: IC7.7 (A_4), R11.2
Sense2-1: Q1.2 (G), R5.1; also elsewhere on the board
Sense2-4: Q4.2 (G), R10.1; also elsewhere on the board
Sense2-7: Q3.2 (G), R9.1; also elsewhere on the board
Sense2-10: Q2.2 (G), R8.1; also elsewhere on the board
